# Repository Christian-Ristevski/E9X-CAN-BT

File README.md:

# E9X-CAN-BT

## Problem Description
Many of the E9X series of BMW cars were manufactured without support for bluetooth music playback. To modernize these cars, many vendors have begun selling bluetooth-AUX modules of different kinds. The modules all come with the same problem, they aren't connected to the car's CAN network and therefore cannot utilize the built-in steering wheel radio controls. Forcing a driver to scramble around with their phone while driving is both inconvenient and unsafe and should prove easy to adress by designing a bluetooth module with CAN read functionality.

## Roadmap
- [x] Choose ICs (Programmable, CAN, Bluetooth)
- [x] Schematic (Communication)
- [x] Schematic (Power)
- [x] PCB layout and routing
- [x] PCB Manufacturing
- [x] PCB Assembly
- [x] Test power electronics
- [ ] Test program upload
- [ ] Functional testing (Whole PCB)
- [ ] Car installation
- [ ] System testing

## Requirements
* Bluetooth audio compatible with all smartphones (A2DP)
* Music controls though steering wheel (CAN bus)
* Invisible installation (Behind Radio)
* Runs from automotive 12 V line (Power electronics)

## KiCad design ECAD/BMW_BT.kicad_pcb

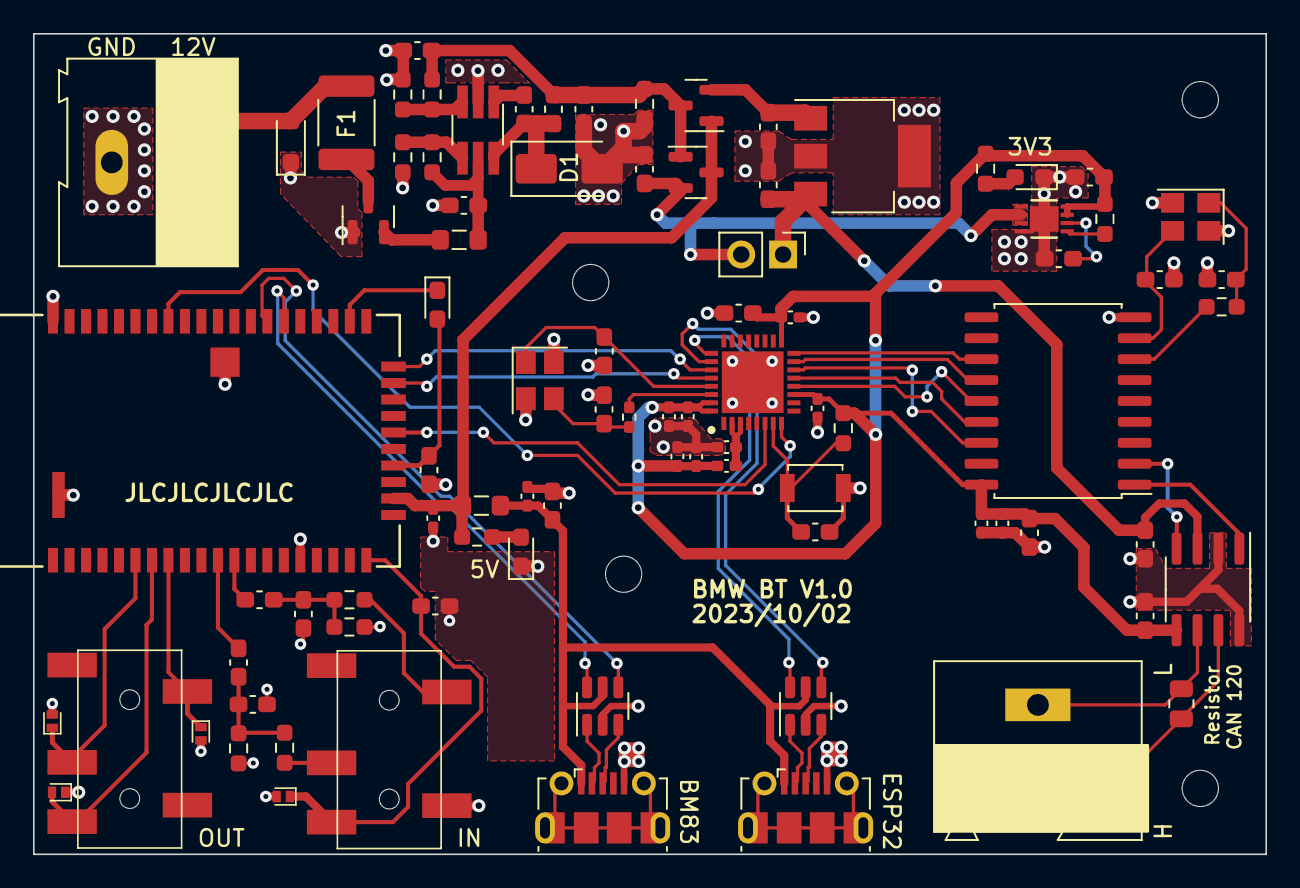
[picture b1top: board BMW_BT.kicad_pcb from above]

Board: 2 copper layers, 74.8 x 49.8 mm, 92 parts (0 on the bottom side), 61 nets.

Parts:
C1, C3, C4, C7, C9, C17, C23, C25: 10u; C_0603_1608Metric_Pad1.08x0.95mm_HandSolder
C2: 10n; C_0603_1608Metric_Pad1.08x0.95mm_HandSolder
C5, C6: 4.7u; C_0603_1608Metric_Pad1.08x0.95mm_HandSolder
C8: 1n; C_0603_1608Metric_Pad1.08x0.95mm_HandSolder
C10, C27: 0.1uF; C_0603_1608Metric_Pad1.08x0.95mm_HandSolder
C11, C12: 470pF; C_0603_1608Metric_Pad1.08x0.95mm_HandSolder
C13, C14: 10uF 10V; C_0603_1608Metric_Pad1.08x0.95mm_HandSolder
C18, C19, C22: 100n; C_0402_1005Metric_Pad0.74x0.62mm_HandSolder
C20: 10u; C_0402_1005Metric_Pad0.74x0.62mm_HandSolder
C21, C24, C37, C38: 0.1u; C_0402_1005Metric_Pad0.74x0.62mm_HandSolder
C26, C36: 1u; C_0402_1005Metric_Pad0.74x0.62mm_HandSolder
C28, C29, C34: 100n; C_0603_1608Metric_Pad1.08x0.95mm_HandSolder
C30, C31: 12p; C_0603_1608Metric_Pad1.08x0.95mm_HandSolder
C32, C33: 10p; C_0603_1608Metric_Pad1.08x0.95mm_HandSolder
C35: 10n; C_0402_1005Metric_Pad0.74x0.62mm_HandSolder
D1: B230A-13-F; D_SMA
D4: CDSOD323-T12LC; D_SOD-323_HandSoldering
D5, D6, D7, D8: 5V; D_SOD-882
D9: Blue; LED_0603_1608Metric_Pad1.05x0.95mm_HandSolder
D10: GREEN; D_0603_1608Metric_Pad1.05x0.95mm_HandSolder
D11: BLUE; LED_0603_1608Metric_Pad1.05x0.95mm_HandSolder
F1: 500mA; Fuse_1812_4532Metric_Pad1.30x3.40mm_HandSolder
FB1: 600 @ 600MHz; L_0805_2012Metric_Pad1.05x1.20mm_HandSolder
FB2: 100 @ 100M; L_0805_2012Metric_Pad1.05x1.20mm_HandSolder
H1, H2, H3, H4: MountingHole; MountingHole_2.2mm_M2
IC1: ESP32-C3; QFN50P500X500X90-33N-D
J1, J7: Screw_Terminal_01x02; TerminalBlock_Altech_AK300-2_P5.00mm
J2, J3: SJ2-35863B1-SMT-TR
J4, J5: USB_B_Micro; USB_Micro-B_Molex-105017-0001
J6: Conn_01x02_Pin; PinHeader_1x02_P2.54mm_Vertical
L1: 14u; L_0603_1608Metric_Pad1.05x0.95mm_HandSolder
L3: 2nH; L_0402_1005Metric_Pad0.77x0.64mm_HandSolder
Q1: RRR040P03TL; SOT-23
Q2, Q3: IRLML6401TRPBF; SOT-23
R1, R6: 100k; R_0603_1608Metric_Pad0.98x0.95mm_HandSolder
R2: 68k; R_0603_1608Metric_Pad0.98x0.95mm_HandSolder
R3: 47k; R_0603_1608Metric_Pad0.98x0.95mm_HandSolder
R4: 8k45; R_0603_1608Metric_Pad0.98x0.95mm_HandSolder
R5: 10k; R_0603_1608Metric_Pad0.98x0.95mm_HandSolder
R7, R8: 1k 1%; R_0603_1608Metric_Pad0.98x0.95mm_HandSolder
R9, R10: 10k 1%; R_0603_1608Metric_Pad0.98x0.95mm_HandSolder
R11, R12: 1k; R_0603_1608Metric_Pad0.98x0.95mm_HandSolder
R13: 22R; R_0603_1608Metric_Pad0.98x0.95mm_HandSolder
R14: 22R; R_0402_1005Metric_Pad0.72x0.64mm_HandSolder
R15: 5k1; R_0603_1608Metric_Pad0.98x0.95mm_HandSolder
R16: 100k; R_0805_2012Metric
SW1: SW_Push; SW_SPST_B3U-1000P
U1: MP2359DJ-LF-P; TSOT-23-6_HandSoldering
U2: MCP1825S; SOT-223-3_TabPin2
U3: MCP1725-3302E/MC; DFN8_2x3MC_MCH
U4, U5: USBLC6-2SC6; SOT-23-6
U6: BM83SM1-00TA; BM83_MCH
U7: MCP2515-xSO; SOIC-18W_7.5x11.6mm_P1.27mm
U8: MCP2562-H-SN; SOIC-8_3.9x4.9mm_P1.27mm
X1: 16MHz; Crystal_SMD_3225-4Pin_3.2x2.5mm
X2: 40MHz; Crystal_SMD_3225-4Pin_3.2x2.5mm

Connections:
3P3_CPU: C9.1, C17.1, C18.1, C19.1, C20.1, C21.1, C22.1, C23.1, C29.1, C35.1, C36.1, C37.1, IC1.11 (VDD3P3_RTC), IC1.17 (VDD3P3_CPU), IC1.31 (VDDA_1), IC1.32 (VDDA_2), L3.1, R5.1, R11.1, R15.1, U3.7 (SENSE), U3.8 (VOUT), U7.18 (VDD), U8.5 (Vio)
+5.3V: C3.1, C4.1, L1.2, Q2.1 (G), Q3.3 (D), R3.1, R6.1
+5V: C6.1, C28.1, J6.1, U2.3 (VO), U8.3 (VDD)
+12V: D4.2 (A2), F1.1, J1.1
/AL: C12.1, C14.1, R8.2, R10.2
/AR: C11.2, C13.1, R7.2, R9.1
/A_R1: J3.3 (R), R7.1
/A_T: J3.2 (T), R8.1
/CANH: J7.2, R16.1, U8.7 (CANH)
/CANL: J7.1, R16.2, U8.6 (CANL)
/LED1: D11.1 (K), U6.32 (LED1)
/RP_Prot: F1.2, Q1.3 (D)
/UART_RXD: IC1.28 (U0TXD), U6.29 (P8_6/UART_RXD)
/UART_TXD: IC1.27 (U0RXD), U6.30 (P8_5/UART_TXD)
/XTAL_MCP1: C31.1, U7.8 (OSC1), X1.3
/XTAL_MCP2: R13.1, U7.7 (OSC2)
/XTAL_MCP_IN: C30.1, R13.2, X1.1
ADAP_IN: C26.1, FB2.1, Q2.3 (D), Q3.1 (G), R12.1, U6.22 (ADAP_IN)
AIL: C14.2, U6.12 (AIL)
AIR: C13.2, U6.11 (AIR)
AOHPL: D7.1 (A1), J2.2 (T), U6.8 (AOHPL)
AOHPM: D6.2 (A2), J2.4 (S), U6.7 (AOHPM)
AOHPR: D5.1 (A1), J2.3 (R), U6.6 (AOHPR)
BUCK_BST: C2.1, U1.1 (BST)
BUCK_EN: R1.2, R2.1, U1.4 (EN)
BUCK_FB: R3.2, R4.1, U1.3 (FB)
BUCK_IN: C1.1, FB1.2, R1.1, U1.5 (IN)
BUCK_SW: C2.2, D1.1 (K), L1.1, U1.6 (SW)
CS_2515: IC1.14 (GPIO8), U7.16 (~CS)
ESP_EN: C34.1, IC1.7 (CHIP_EN), R15.2, SW1.1
GND: C1.2, C3.2, C4.2, C5.2, C6.2, C7.2, C8.2, C9.2, C10.2, C11.1, C12.2, C17.2, C18.2, C19.2, C20.2, C21.2, C22.2, C23.2, C24.2, C25.2, C26.2, C27.2, C28.2, C29.2, C30.2, C31.2, C32.2, C33.2, C34.2, C35.2, C36.2, C37.2, C38.2, D1.2 (A), D4.1 (A1), D5.2 (A2), D6.1 (A1), D7.2 (A2), D8.2 (A2), D9.1 (K), D10.1 (K), IC1.33 (GND), J1.2, J3.1 (S), J4.5 (GND), J5.5 (GND), Q1.1 (G), R2.2, R4.2, R6.2, R9.2, R10.1, SW1.2, U1.2 (GND), U2.2 (GND), U3.4 (GND), U3.9 (EP), U4.2 (GND), U5.2 (GND), U6.16 (GND), U6.50 (GND), U6.56 (GND), U6.57 (GND), U7.9 (VSS), U8.2 (VSS), U8.8 (STBY), X1.2, X1.4, X2.2, X2.4
INT_2515: IC1.16 (GPIO10), U7.12 (~INT)
LD33_CDELAY: C8.1, U3.6 (CDELAY)
LD33_PWRGD: R5.2, U3.5 (PWRGD)
MFB: IC1.6 (GPIO2), U6.26 (PWR(MFB))
unnamed: C33.1, R14.2, X2.3
unnamed: D9.2 (A), R11.2
unnamed: D10.2 (A), R12.2
unnamed: FB1.1, Q1.2 (S)
P3_2: C10.1, D8.1 (A1), J3.4 (S), U6.20 (P3_2)
RST_N: IC1.8 (GPIO3), U6.43 (RST_N)
RXCAN: U7.2 (RXCAN), U8.4 (RXD)
SCK_2515: IC1.15 (GPIO9), U7.13 (SCK)
SI_2515: IC1.12 (MTCK), U7.14 (SI)
SO_2515: IC1.13 (MTDO), U7.15 (SO)
SW_5.3V: C5.1, Q3.2 (S), U2.1 (VI)
SW_USB: C7.1, J6.2, Q2.2 (S), U3.1 (VIN), U3.2 (VIN), U3.3 (*SHDN)
SYS_PWR: C27.1, D11.2 (A), U6.24 (SYS_PWR)
TXCAN: U7.1 (TXCAN), U8.1 (TXD)
USB2_CONN_D+: J5.3 (D+), U5.3 (I/O2)
USB2_CONN_D-: J5.2 (D-), U5.1 (I/O1)
USB2_D+: U5.4 (I/O2), U6.37 (DP)
USB2_D-: U5.6 (I/O1), U6.36 (DM)
USB_5V: C24.1, C25.1, FB2.2, J4.1 (VBUS), J5.1 (VBUS), U4.5 (VBUS), U5.5 (VBUS)
USB_CONN_D+: J4.3 (D+), U4.3 (I/O2)
USB_CONN_D-: J4.2 (D-), U4.1 (I/O1)
USB_D+: IC1.26 (GPIO19), U4.4 (I/O2)
USB_D-: IC1.25 (GPIO18), U4.6 (I/O1)
VDD3P3: C38.1, IC1.2 (VDD3P3_1), IC1.3 (VDD3P3_2), L3.2
XTAL_N: C32.1, IC1.29 (XTAL_N), X2.1
XTAL_P: IC1.30 (XTAL_P), R14.1

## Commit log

2023-07-22 Create BMW_BT.ino
    Initial commit
2023-07-23 Update BMW_BT.ino
    comment unused switch cases
2024-02-14 Uploaded ECAD files
2024-02-15 Added Images
2024-02-15 Update README.md picture
2024-02-15 Update profile URL
